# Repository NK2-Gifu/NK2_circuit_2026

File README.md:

# NK2_circuit_2026
回路図と基盤データを保管するところ

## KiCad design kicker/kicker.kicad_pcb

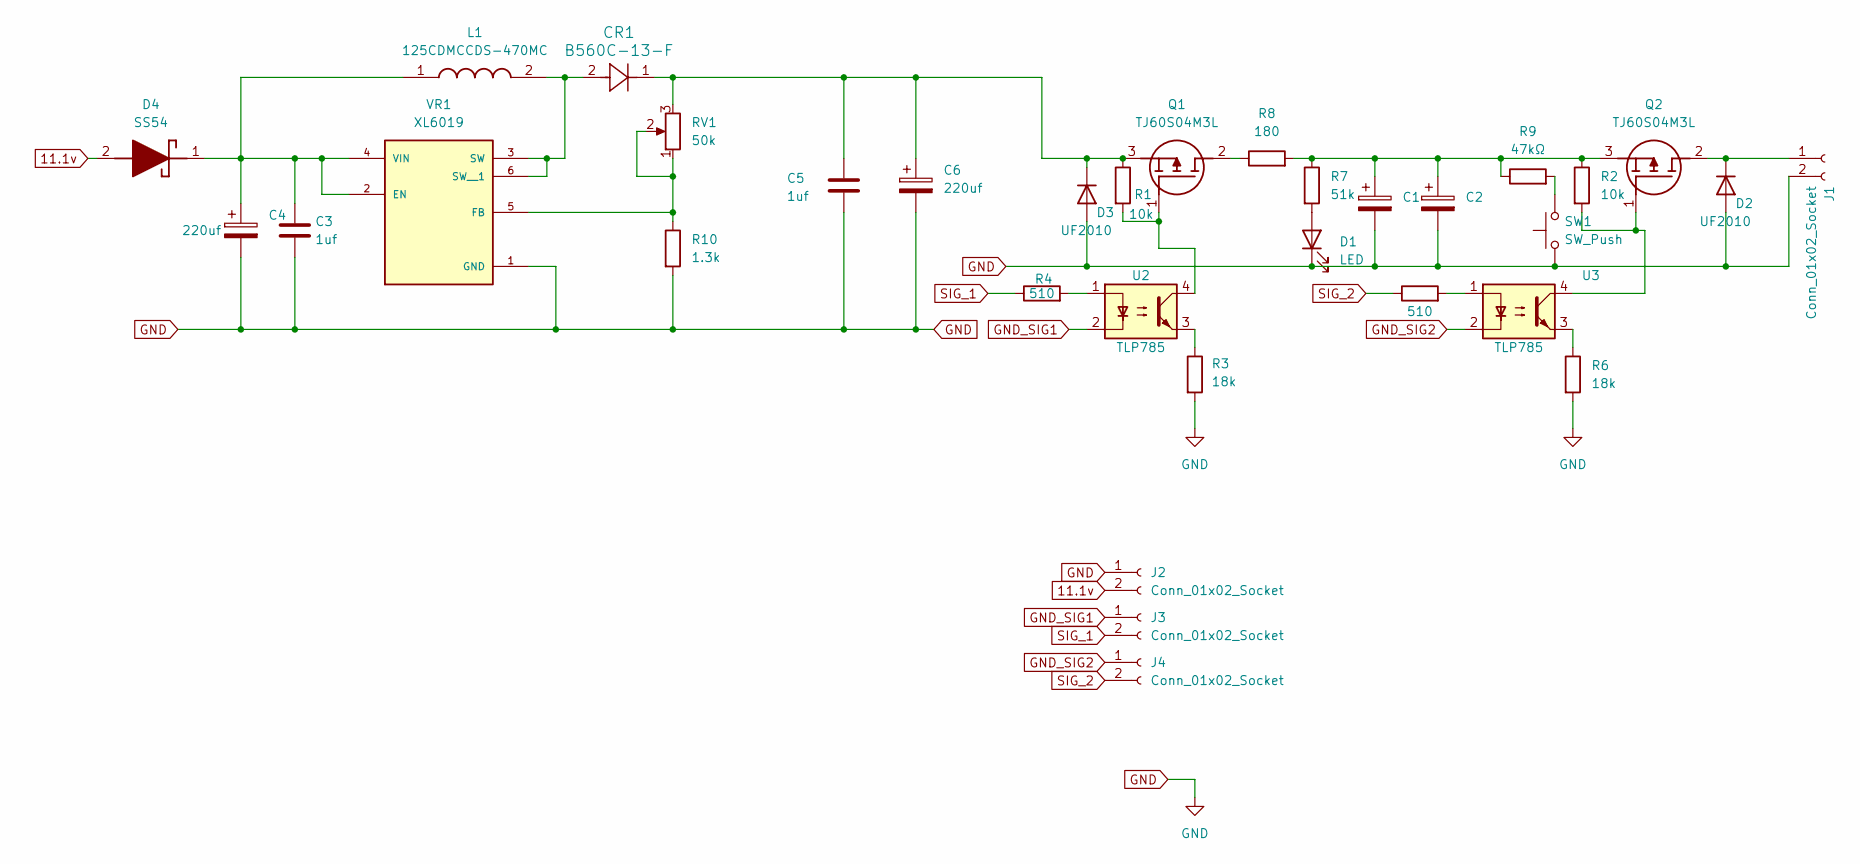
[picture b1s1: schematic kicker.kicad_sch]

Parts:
C1, C2: 2200F; CP_Radial_D16.0mm_P7.50mm
C3, C5: 1uf; C_1206_3216Metric; LCSC C1848
C4, C6: 220uf; C_Elec_10x10.2; LCSC C3358
CR1: B560C-13-F; SMC_DIO; LCSC C6807784
D1: LED; LED_D3.0mm
D2, D3: UF2010; D_DO-15_P10.16mm_Horizontal
D4: SS54; DIOM5026X262N; Manufacturer_Part_Number SS54; LCSC C22452
J1, J2, J3, J4: Conn_01x02_Socket; JST_XH_B2B-XH-A_1x02_P2.50mm_Vertical
L1: 125CDMCCDS-470MC; INDPM134126X500N; Manufacturer_Part_Number 125CDMCCDS-470MC; LCSC C3020208
Q1, Q2: TJ60S04M3L; Manufacturer_Part_Number TJ60S04M3L
R1, R2: 10k; R_1206_3216Metric; LCSC C1489
R3, R6: 18k; R_1206_3216Metric; LCSC C1469
R4, R5: 510; R_0603_1608Metric; LCSC C23193
R7: 51k; R_1206_3216Metric; LCSC C1489
R8: 180; R_2512_6332Metric; LCSC C82626
R9: 47kΩ; R_0603_1608Metric; LCSC C25600
R10: 1.3k; R_1206_3216Metric; LCSC C1471
RV1: 50k; Potentiometer_Vishay_T73YP_Vertical
SW1: SW_Push; SW_PUSH_6mm_H7.3mm
U2, U3: TLP785; DIP-4_W7.62mm
VR1: XL6019; xl6019; PARTREV 1.1

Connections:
11.1v: D4.2 (A), J2.2
GND: C1.2, C2.2, C3.2, C4.2, C5.2, C6.2, D1.1 (K), D2.2 (A), D3.2 (A), J1.2, J2.1, R3.2, R6.2, R10.2, SW1.1, VR1.1 (GND)
GND_SIG1: J3.1, U2.2
GND_SIG2: J4.1, U3.2
unnamed: D1.2 (A), R7.2
unnamed: D2.1 (K), J1.1, Q2.2 (D)
unnamed: C5.1, C6.1, CR1.1, D3.1 (K), Q1.3 (S), R1.1, RV1.3
unnamed: C3.1, C4.1, D4.1 (K), L1.1, VR1.2 (EN), VR1.4 (VIN)
unnamed: Q1.2 (D), R8.1
unnamed: Q1.1 (G), R1.2, U2.4
unnamed: Q2.1 (G), R2.2, U3.4
unnamed: C1.1, C2.1, Q2.3 (S), R2.1, R7.1, R8.2, R9.1
unnamed: R3.1, U2.3
unnamed: R4.2, U2.1
unnamed: R5.2, U3.1
unnamed: R6.1, U3.3
unnamed: R9.2, SW1.2
unnamed: R10.1, RV1.1, RV1.2, VR1.5 (FB)
unnamed: CR1.2, L1.2, VR1.3 (SW), VR1.6 (SW__1)
SIG_1: J3.2, R4.1
SIG_2: J4.2, R5.1

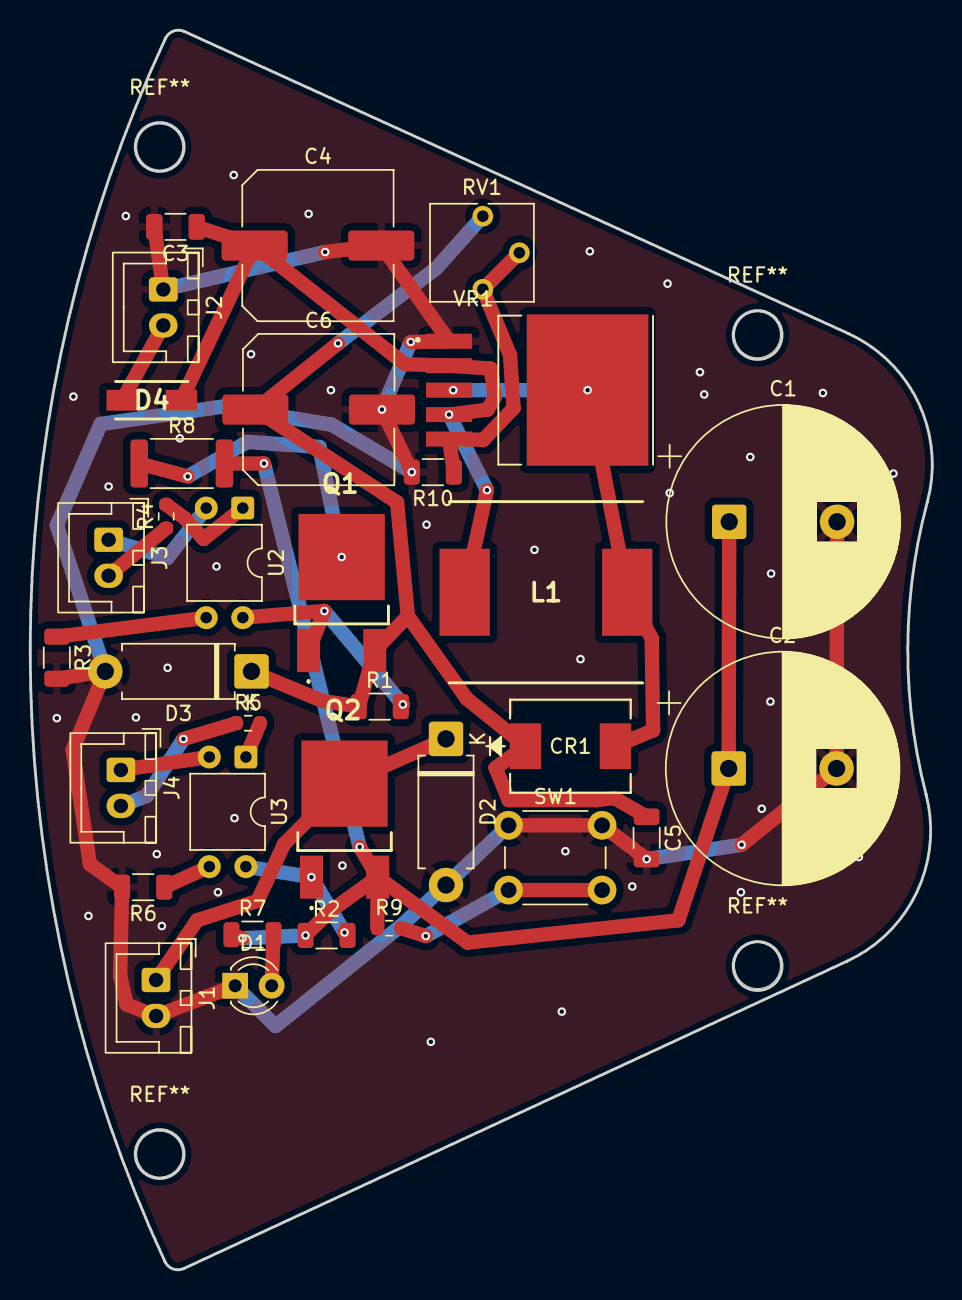
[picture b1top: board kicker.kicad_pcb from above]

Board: 2 copper layers, 62.7 x 86.2 mm, 33 parts (0 on the bottom side), 21 nets.

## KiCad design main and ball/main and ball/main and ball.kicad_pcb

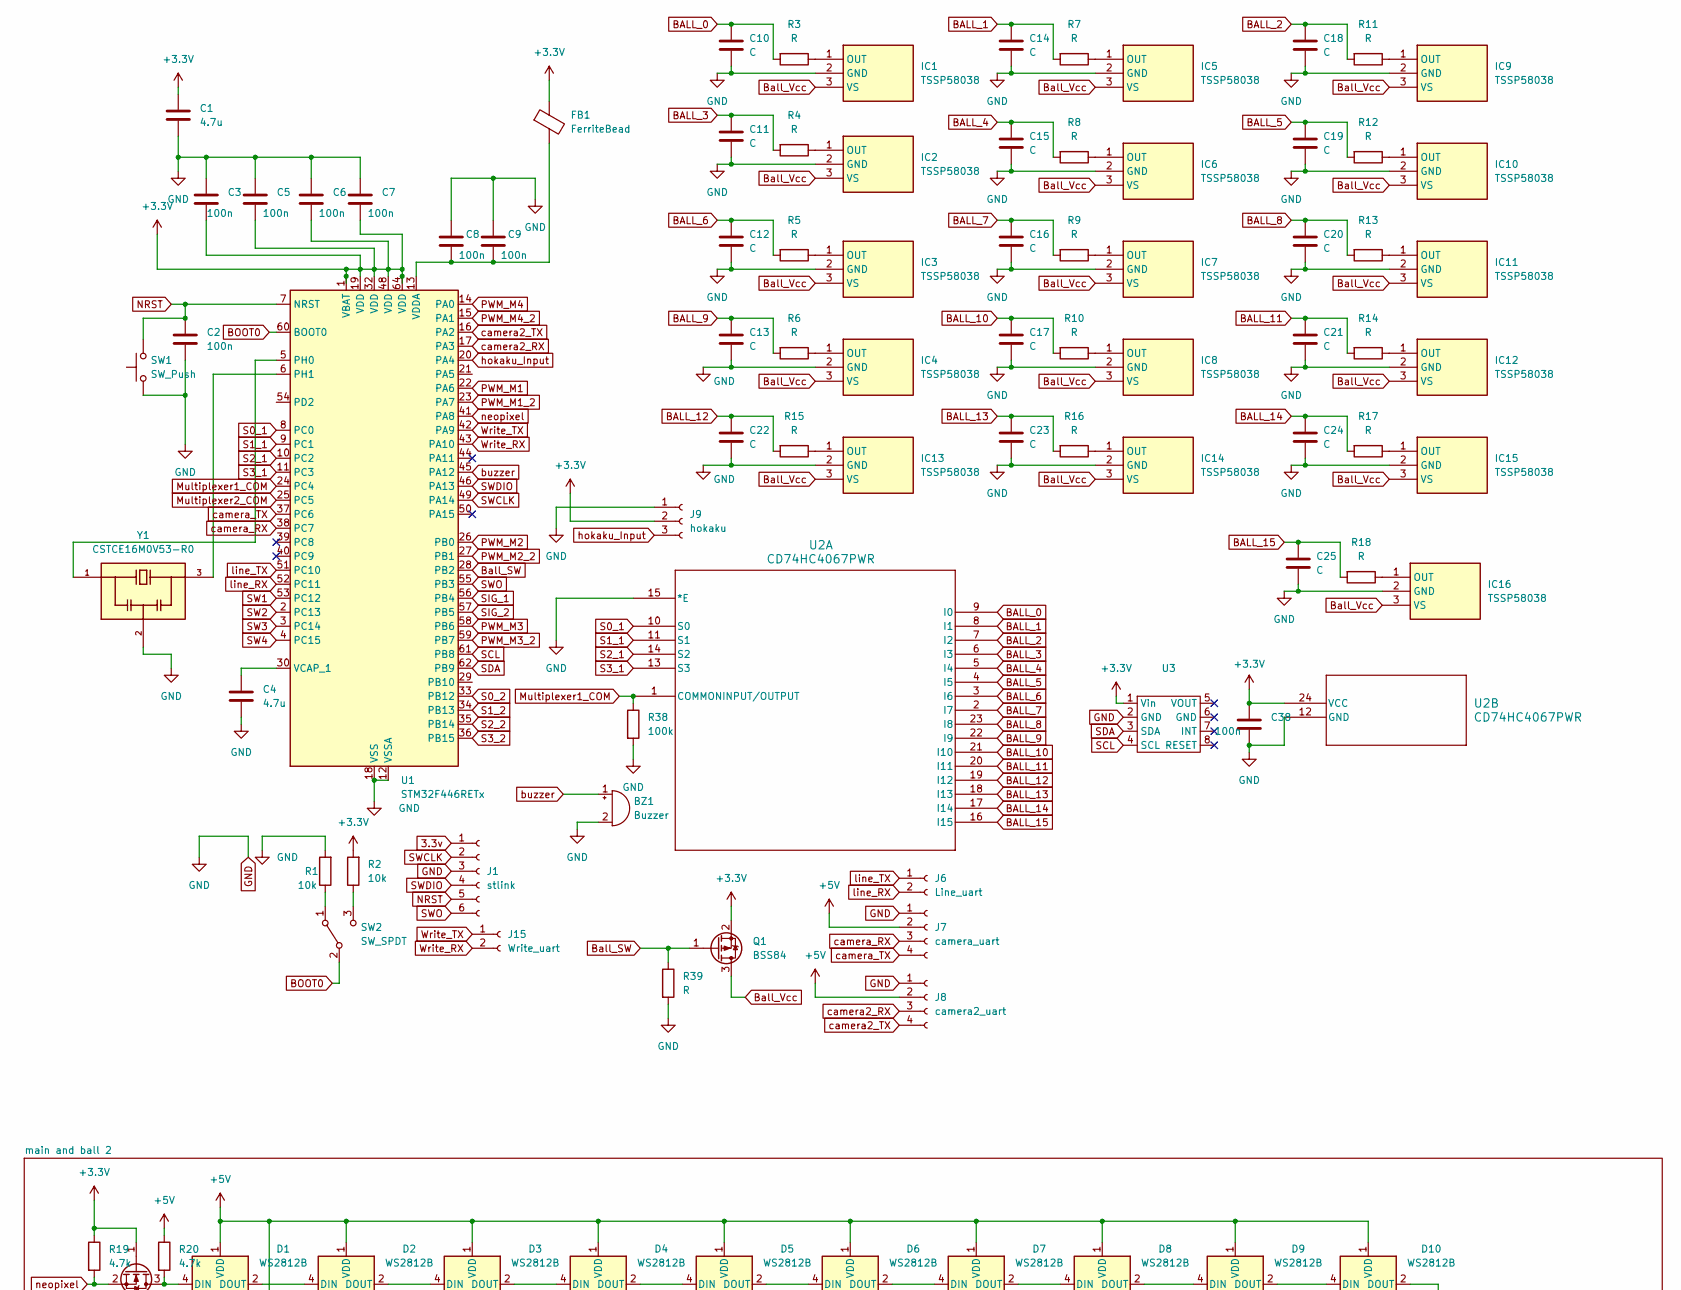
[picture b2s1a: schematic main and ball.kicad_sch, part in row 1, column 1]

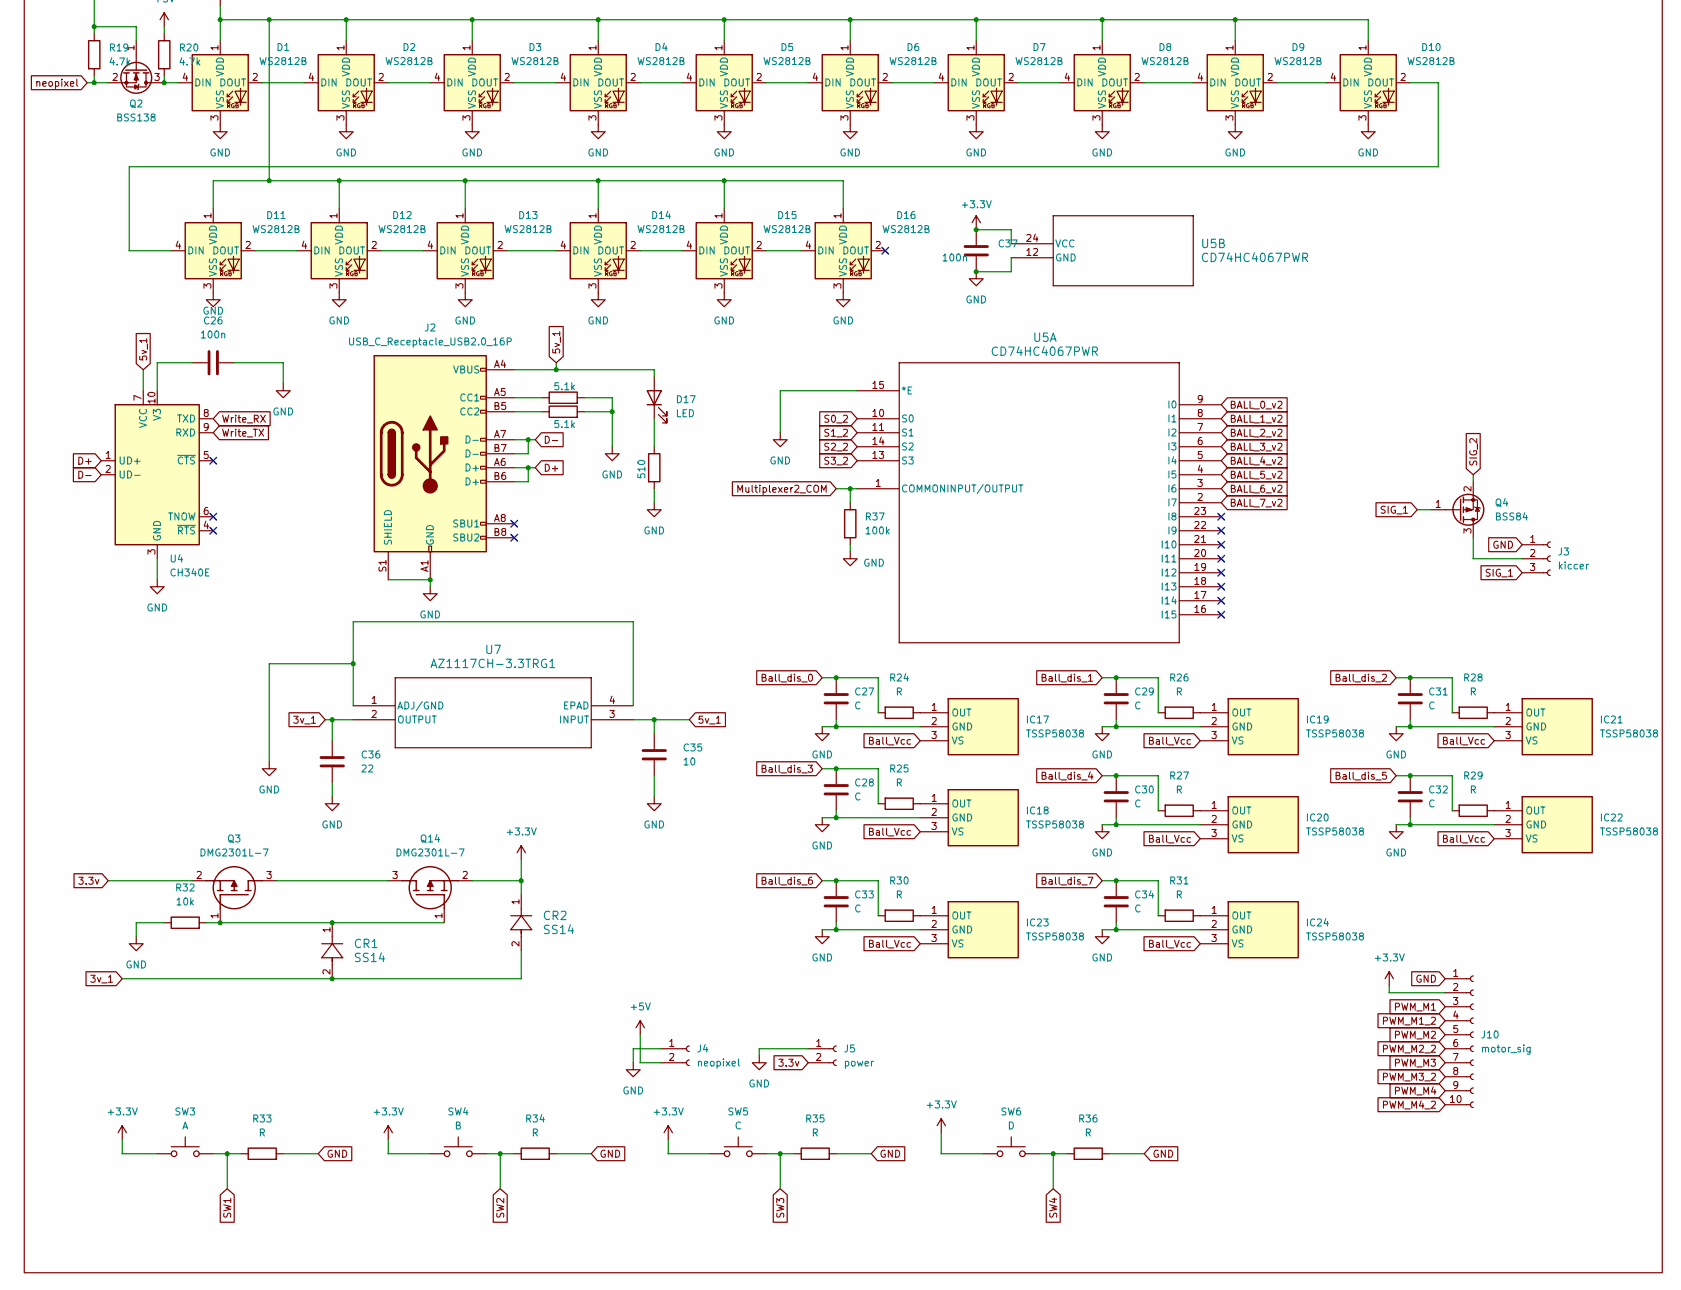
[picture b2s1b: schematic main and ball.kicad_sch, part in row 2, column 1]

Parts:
BZ1: Buzzer; Buzzer_TDK_PS1240P02BT_D12.2mm_H6.5mm
C1, C4: 4.7u; C_0402_1005Metric; LCSC C23733
C2, C3, C5, C6, C7, C8, C9, C26, C37, C38: 100n; C_0402_1005Metric; LCSC C1525
C10, C11, C12, C13, C14, C15, C16, C17, C18, C19, C20, C21, C22, C23, C24, C25, C27, C28, C29, C30, C31, C32, C33, C34: C; C_0603_1608Metric
C35: 10; C_0603_1608Metric; LCSC C1691
C36: 22; C_0603_1608Metric; LCSC C1859
CR1, CR2: SS14; CR_SMA_403AE_OSI; LCSC C2480
D1, D2, D3, D4, D5, D6, D7, D8, D9, D10, D11, D12, D13, D14, D15, D16: WS2812B; LED_WS2812B_PLCC4_5.0x5.0mm_P3.2mm
D17: LED; LED_0603_1608Metric; LCSC C2286
FB1: FerriteBead; R_0603_1608Metric; LCSC C275451
IC1, IC2, IC3, IC4, IC5, IC6, IC7, IC8, IC9, IC10, IC11, IC12, IC13, IC14, IC15, IC16, IC17, IC18, IC19, IC20, IC21, IC22, IC23, IC24: TSSP58038; Manufacturer_Part_Number TSSP58038
J1: stlink; JST_XH_B6B-XH-A_1x06_P2.50mm_Vertical
J2: USB_C_Receptacle_USB2.0_16P; USB_C_Receptacle_XKB_U262-16XN-4BVC11; LCSC C393939
J3: kiccer; JST_XH_B3B-XH-A_1x03_P2.50mm_Vertical
J4: neopixel; JST_XH_B2B-XH-A_1x02_P2.50mm_Vertical
J5: power; JST_XH_B2B-XH-A_1x02_P2.50mm_Vertical
J6: Line_uart; JST_XH_B2B-XH-A_1x02_P2.50mm_Vertical
J7: camera_uart; JST_PH_B4B-PH-K_1x04_P2.00mm_Vertical
J8: camera2_uart; JST_PH_B4B-PH-K_1x04_P2.00mm_Vertical
J9: hokaku; JST_XH_B3B-XH-A_1x03_P2.50mm_Vertical
J10: motor_sig; CONN_302-R101_OST
J15: Write_uart; JST_XH_B2B-XH-A_1x02_P2.50mm_Vertical
Q1, Q4: BSS84; SOT-23; LCSC C112238
Q2: BSS138; SOT-23; LCSC C52895
Q3, Q14: DMG2301L-7; SOT96P240X115-3N; Manufacturer_Part_Number DMG2301L-7; LCSC C102619
R1, R2, R32: 10k; R_0603_1608Metric
R3, R4, R5, R6, R7, R8, R9, R10, R11, R12, R13, R14, R15, R16, R17, R18, R24, R25, R26, R27, R28, R29, R30, R31: R; R_0603_1608Metric
R19, R20: 4.7k; R_0603_1608Metric
R21, R22: 5.1k; R_0603_1608Metric
R23: 510; R_0603_1608Metric
R33, R34, R35, R36: R; R_Axial_DIN0207_L6.3mm_D2.5mm_P10.16mm_Horizontal
R37, R38: 100k; R_0603_1608Metric
R39: R
SW1: SW_Push; SW_PUSH_6mm_H7.3mm
SW2: SW_SPDT; 名称未設定
SW3: A; SW_PUSH_6mm_H7.3mm
SW4: B; SW_PUSH_6mm_H7.3mm
SW5: C; SW_PUSH_6mm_H7.3mm
SW6: D; SW_PUSH_6mm_H7.3mm
U1: STM32F446RETx; LQFP-64_10x10mm_P0.5mm; LCSC C69336
U2, U5: CD74HC4067PWR; TSSOP24_4P5X7P9_TEX; LCSC C47361296
U3: bno055
U4: CH340E; MSOP-10_3x3mm_P0.5mm; LCSC C99652
U7: AZ1117CH-3.3TRG1; SOT-223_DIO; LCSC C92102
Y1: CSTCE16M0V53-R0; OSC_CSTCE16M0V53-R0; PARTREV 10/24/2022; LCSC C32180

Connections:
3.3v: J1.1, J5.2, Q3.2 (S)
3v_1: C36.1, CR1.2, CR2.2, U7.2 (OUTPUT)
5v_1: C35.1, D17.2 (A), J2.A4 (VBUS), J2.A9 (VBUS), J2.B4 (VBUS), J2.B9 (VBUS), U4.7 (VCC), U7.3 (INPUT)
+3.3V: C1.1, C3.2, C5.2, C6.2, C7.2, C37.1, C38.1, CR2.1, FB1.1, J9.2, J10.2, Q1.2 (S), Q2.1 (G), Q14.2 (S), R2.2, R19.1, SW3.1, SW4.1, SW5.1, SW6.1, U1.1 (VBAT), U1.19 (VDD), U1.32 (VDD), U1.48 (VDD), U1.64 (VDD), U2.24 (VCC), U3.1 (Vin), U5.24 (VCC)
+5V: D1.1 (VDD), D2.1 (VDD), D3.1 (VDD), D4.1 (VDD), D5.1 (VDD), D6.1 (VDD), D7.1 (VDD), D8.1 (VDD), D9.1 (VDD), D10.1 (VDD), D11.1 (VDD), D12.1 (VDD), D13.1 (VDD), D14.1 (VDD), D15.1 (VDD), D16.1 (VDD), J4.2, J7.2, J8.2, R20.1
BALL_0: C10.2, R3.2, U2.9 (I0)
BALL_0_v2: U5.9 (I0)
BALL_1: C14.2, R7.2, U2.8 (I1)
BALL_1_v2: U5.8 (I1)
BALL_2: C18.2, R11.2, U2.7 (I2)
BALL_2_v2: U5.7 (I2)
BALL_3: C11.2, R4.2, U2.6 (I3)
BALL_3_v2: U5.6 (I3)
BALL_4: C15.2, R8.2, U2.5 (I4)
BALL_4_v2: U5.5 (I4)
BALL_5: C19.2, R12.2, U2.4 (I5)
BALL_5_v2: U5.4 (I5)
BALL_6: C12.2, R5.2, U2.3 (I6)
BALL_6_v2: U5.3 (I6)
BALL_7: C16.2, R9.2, U2.2 (I7)
BALL_7_v2: U5.2 (I7)
BALL_8: C20.2, R13.2, U2.23 (I8)
BALL_9: C13.2, R6.2, U2.22 (I9)
BALL_10: C17.2, R10.2, U2.21 (I10)
BALL_11: C21.2, R14.2, U2.20 (I11)
BALL_12: C22.2, R15.2, U2.19 (I12)
BALL_13: C23.2, R16.2, U2.18 (I13)
BALL_14: C24.2, R17.2, U2.17 (I14)
BALL_15: C25.2, R18.2, U2.16 (I15)
BOOT0: SW2.2 (B), U1.60 (BOOT0)
Ball_SW: Q1.1 (G), R39.1, U1.28 (PB2)
Ball_Vcc: IC1.3 (VS), IC2.3 (VS), IC3.3 (VS), IC4.3 (VS), IC5.3 (VS), IC6.3 (VS), IC7.3 (VS), IC8.3 (VS), IC9.3 (VS), IC10.3 (VS), IC11.3 (VS), IC12.3 (VS), IC13.3 (VS), IC14.3 (VS), IC15.3 (VS), IC16.3 (VS), IC17.3 (VS), IC18.3 (VS), IC19.3 (VS), IC20.3 (VS), IC21.3 (VS), IC22.3 (VS), IC23.3 (VS), IC24.3 (VS), Q1.3 (D)
Ball_dis_0: C27.2, R24.2
Ball_dis_1: C29.2, R26.2
Ball_dis_2: C31.2, R28.2
Ball_dis_3: C28.2, R25.2
Ball_dis_4: C30.2, R27.2
Ball_dis_5: C32.2, R29.2
Ball_dis_6: C33.2, R30.2
Ball_dis_7: C34.2, R31.2
D+: J2.A6 (D+), J2.B6 (D+), U4.1 (UD+)
D-: J2.A7 (D-), J2.B7 (D-), U4.2 (UD-)
GND: BZ1.2 (-), C1.2, C2.2, C3.1, C4.2, C5.1, C6.1, C7.1, C8.1, C9.1, C10.1, C11.1, C12.1, C13.1, C14.1, C15.1, C16.1, C17.1, C18.1, C19.1, C20.1, C21.1, C22.1, C23.1, C24.1, C25.1, C26.2, C27.1, C28.1, C29.1, C30.1, C31.1, C32.1, C33.1, C34.1, C35.2, C36.2, C37.2, C38.2, D1.3 (VSS), D2.3 (VSS), D3.3 (VSS), D4.3 (VSS), D5.3 (VSS), D6.3 (VSS), D7.3 (VSS), D8.3 (VSS), D9.3 (VSS), D10.3 (VSS), D11.3 (VSS), D12.3 (VSS), D13.3 (VSS), D14.3 (VSS), D15.3 (VSS), D16.3 (VSS), IC1.2 (GND), IC2.2 (GND), IC3.2 (GND), IC4.2 (GND), IC5.2 (GND), IC6.2 (GND), IC7.2 (GND), IC8.2 (GND), IC9.2 (GND), IC10.2 (GND), IC11.2 (GND), IC12.2 (GND), IC13.2 (GND), IC14.2 (GND), IC15.2 (GND), IC16.2 (GND), IC17.2 (GND), IC18.2 (GND), IC19.2 (GND), IC20.2 (GND), IC21.2 (GND), IC22.2 (GND), IC23.2 (GND), IC24.2 (GND), J1.3, J2.A1 (GND), J2.A12 (GND), J2.B1 (GND), J2.B12 (GND), J2.S1 (SHIELD), J3.1, J4.1, J5.1, J7.1, J8.1, J9.1, J10.1, R1.2, R21.2, R22.2, R23.2, R32.1, R33.2, R34.2, R35.2, R36.2, R37.2, R38.2, R39.2, SW1.1, U1.12 (VSSA), U1.18 (VSS), U1.31 (VSS), U1.47 (VSS), U1.63 (VSS), U2.12 (GND), U2.15 (*E), U3.2 (GND), U4.3 (GND), U5.12 (GND), U5.15 (*E), U7.1 (ADJ/GND), U7.4 (EPAD), Y1.2
Multiplexer1_COM: R38.1, U1.24 (PC4), U2.1 (COMMONINPUT/OUTPUT)
Multiplexer2_COM: R37.1, U1.25 (PC5), U5.1 (COMMONINPUT/OUTPUT)
NRST: C2.1, J1.5, SW1.2, U1.7 (NRST)
unnamed: D1.4 (DIN), Q2.3 (D), R20.2
unnamed: D1.2 (DOUT), D2.4 (DIN)
unnamed: D2.2 (DOUT), D3.4 (DIN)
unnamed: D3.2 (DOUT), D4.4 (DIN)
unnamed: D4.2 (DOUT), D5.4 (DIN)
unnamed: D5.2 (DOUT), D6.4 (DIN)
unnamed: D6.2 (DOUT), D7.4 (DIN)
unnamed: D7.2 (DOUT), D8.4 (DIN)
unnamed: D8.2 (DOUT), D9.4 (DIN)
unnamed: D9.2 (DOUT), D10.4 (DIN)
unnamed: D10.2 (DOUT), D11.4 (DIN)
unnamed: D11.2 (DOUT), D12.4 (DIN)
unnamed: D12.2 (DOUT), D13.4 (DIN)
unnamed: D13.2 (DOUT), D14.4 (DIN)
unnamed: D14.2 (DOUT), D15.4 (DIN)
unnamed: D15.2 (DOUT), D16.4 (DIN)
unnamed: D17.1 (K), R23.1
unnamed: IC1.1 (OUT), R3.1
unnamed: IC2.1 (OUT), R4.1
unnamed: IC3.1 (OUT), R5.1
unnamed: IC4.1 (OUT), R6.1
unnamed: IC5.1 (OUT), R7.1
unnamed: IC6.1 (OUT), R8.1
unnamed: IC7.1 (OUT), R9.1
unnamed: IC8.1 (OUT), R10.1
unnamed: IC9.1 (OUT), R11.1
unnamed: IC10.1 (OUT), R12.1
unnamed: IC11.1 (OUT), R13.1
unnamed: IC12.1 (OUT), R14.1
unnamed: IC13.1 (OUT), R15.1
unnamed: IC14.1 (OUT), R16.1
unnamed: IC15.1 (OUT), R17.1
unnamed: IC16.1 (OUT), R18.1
unnamed: IC17.1 (OUT), R24.1
unnamed: IC18.1 (OUT), R25.1
unnamed: IC19.1 (OUT), R26.1
unnamed: IC20.1 (OUT), R27.1
unnamed: IC21.1 (OUT), R28.1
unnamed: IC22.1 (OUT), R29.1
unnamed: IC23.1 (OUT), R30.1
unnamed: IC24.1 (OUT), R31.1
unnamed: J2.A5 (CC1), R21.1
unnamed: J2.B5 (CC2), R22.1
unnamed: J3.2, Q4.3 (D)
unnamed: Q3.3 (D), Q14.3 (D)
unnamed: CR1.1, Q3.1 (G), Q14.1 (G), R32.2
unnamed: R1.1, SW2.1 (A)
unnamed: R2.1, SW2.3 (C)
unnamed: U1.5 (PH0), Y1.1
unnamed: U1.6 (PH1), Y1.3
unnamed: C4.1, U1.30 (VCAP_1)
unnamed: C8.2, C9.2, FB1.2, U1.13 (VDDA)
unnamed: C26.1, U4.10 (V3)
PWM_M1: J10.3, U1.22 (PA6)
PWM_M1_2: J10.4, U1.23 (PA7)
PWM_M2: J10.5, U1.26 (PB0)
PWM_M2_2: J10.6, U1.27 (PB1)
PWM_M3: J10.7, U1.58 (PB6)
PWM_M3_2: J10.8, U1.59 (PB7)
PWM_M4: J10.9, U1.14 (PA0)
PWM_M4_2: J10.10, U1.15 (PA1)
S0_1: U1.8 (PC0), U2.10 (S0)
S0_2: U1.33 (PB12), U5.10 (S0)
S1_1: U1.9 (PC1), U2.11 (S1)
S1_2: U1.34 (PB13), U5.11 (S1)
S2_1: U1.10 (PC2), U2.14 (S2)
S2_2: U1.35 (PB14), U5.14 (S2)
S3_1: U1.11 (PC3), U2.13 (S3)
S3_2: U1.36 (PB15), U5.13 (S3)
SCL: U1.61 (PB8), U3.4 (SCL)
SDA: U1.62 (PB9), U3.3 (SDA)
SIG_1: J3.3, Q4.1 (G), U1.56 (PB4)
SIG_2: Q4.2 (S), U1.57 (PB5)
SW1: R33.1, SW3.2, U1.53 (PC12)
SW2: R34.1, SW4.2, U1.2 (PC13)
SW3: R35.1, SW5.2, U1.3 (PC14)
SW4: R36.1, SW6.2, U1.4 (PC15)
SWCLK: J1.2, U1.49 (PA14)
SWDIO: J1.4, U1.46 (PA13)
SWO: J1.6, U1.55 (PB3)
Write_RX: J15.2, U1.43 (PA10), U4.8 (TXD)
Write_TX: J15.1, U1.42 (PA9), U4.9 (RXD)
buzzer: BZ1.1 (+), U1.45 (PA12)
camera2_RX: J8.3, U1.17 (PA3)
camera2_TX: J8.4, U1.16 (PA2)
camera_RX: J7.3, U1.38 (PC7)
camera_TX: J7.4, U1.37 (PC6)
hokaku_Input: J9.3, U1.20 (PA4)
line_RX: J6.2, U1.52 (PC11)
line_TX: J6.1, U1.51 (PC10)
neopixel: Q2.2 (S), R19.2, U1.41 (PA8)

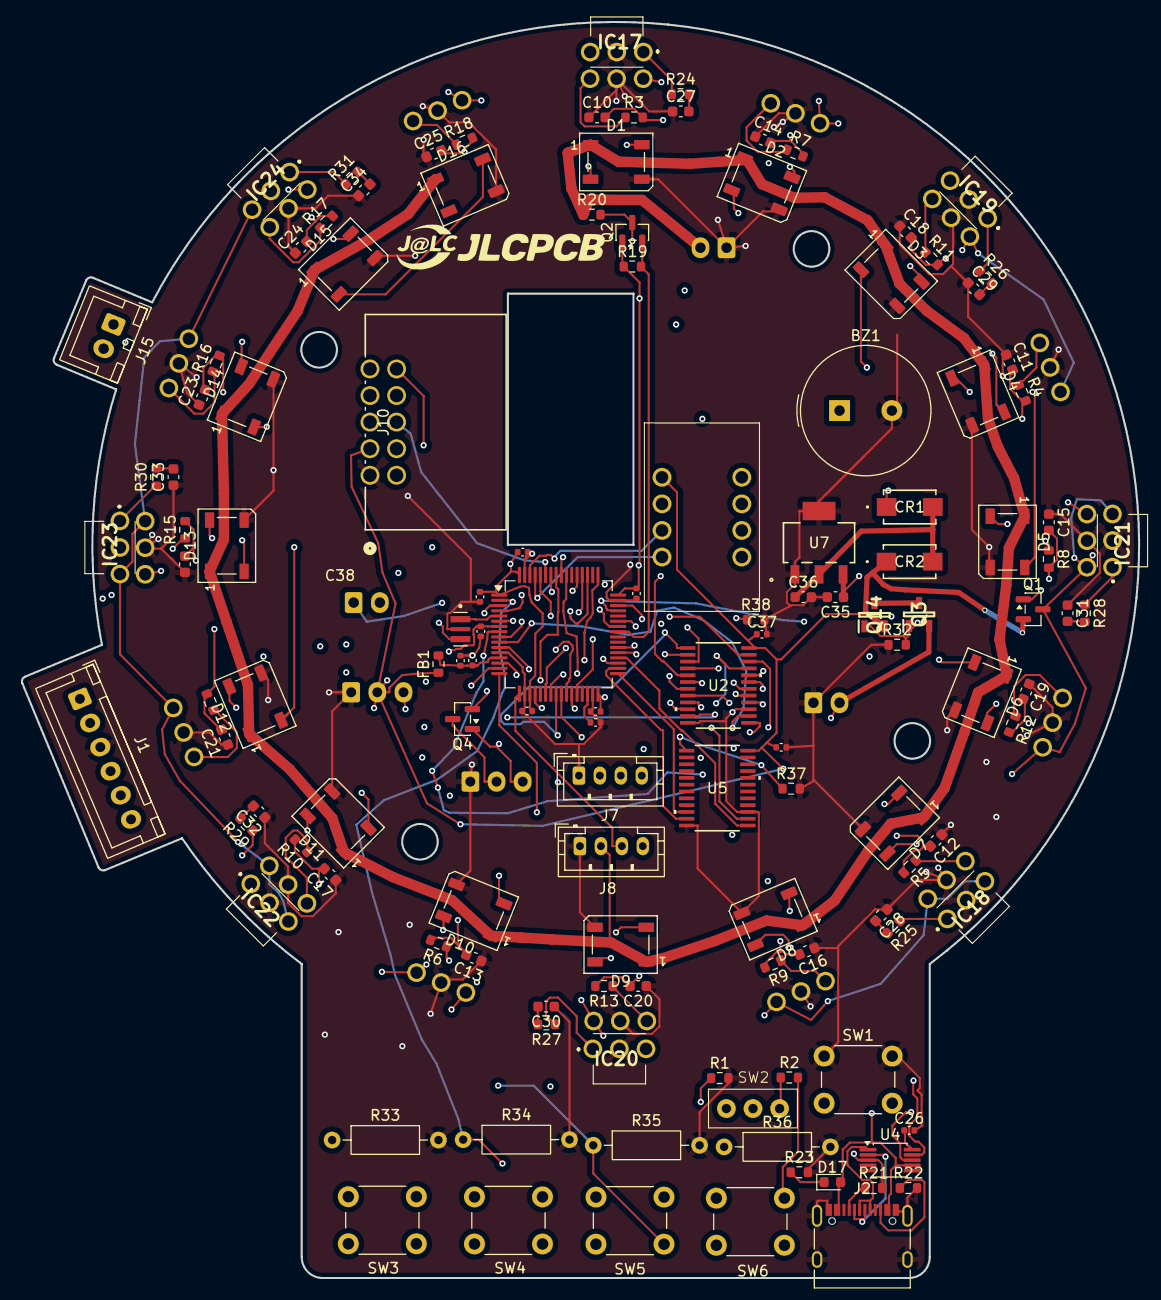
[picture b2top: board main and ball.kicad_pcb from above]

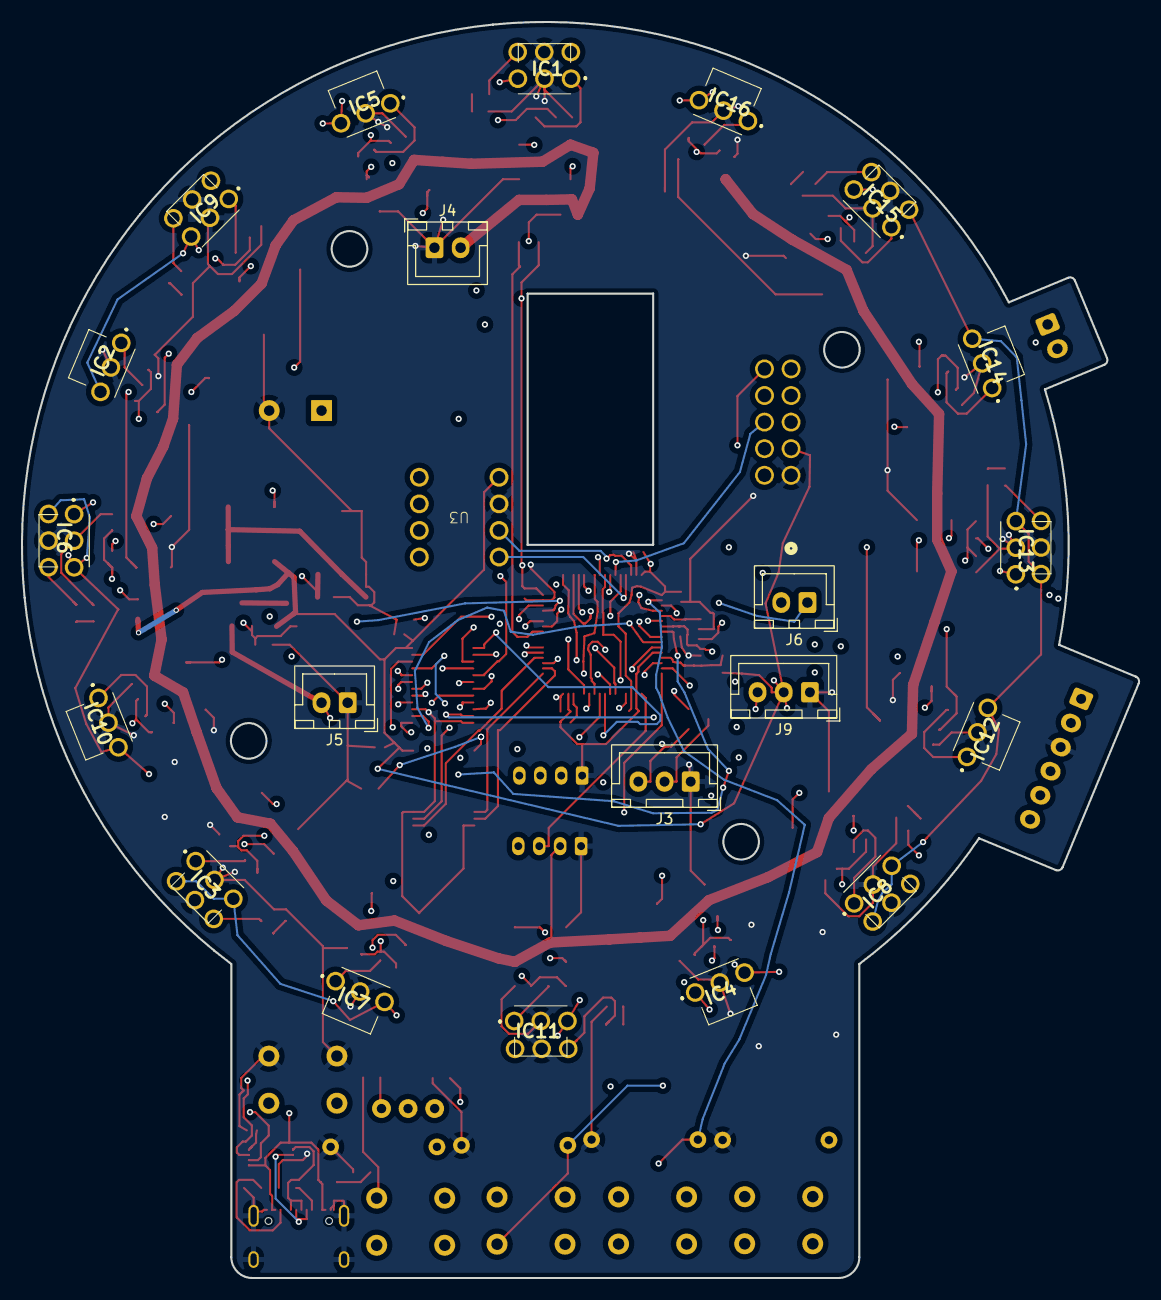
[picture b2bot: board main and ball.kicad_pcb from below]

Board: 4 copper layers, 106.7 x 120.0 mm, 150 parts (21 on the bottom side), 129 nets.
